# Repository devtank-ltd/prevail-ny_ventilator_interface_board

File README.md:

# prevail-ny_ventilator_interface_board
Interface board for PREVAIL-NY emergency ventilator

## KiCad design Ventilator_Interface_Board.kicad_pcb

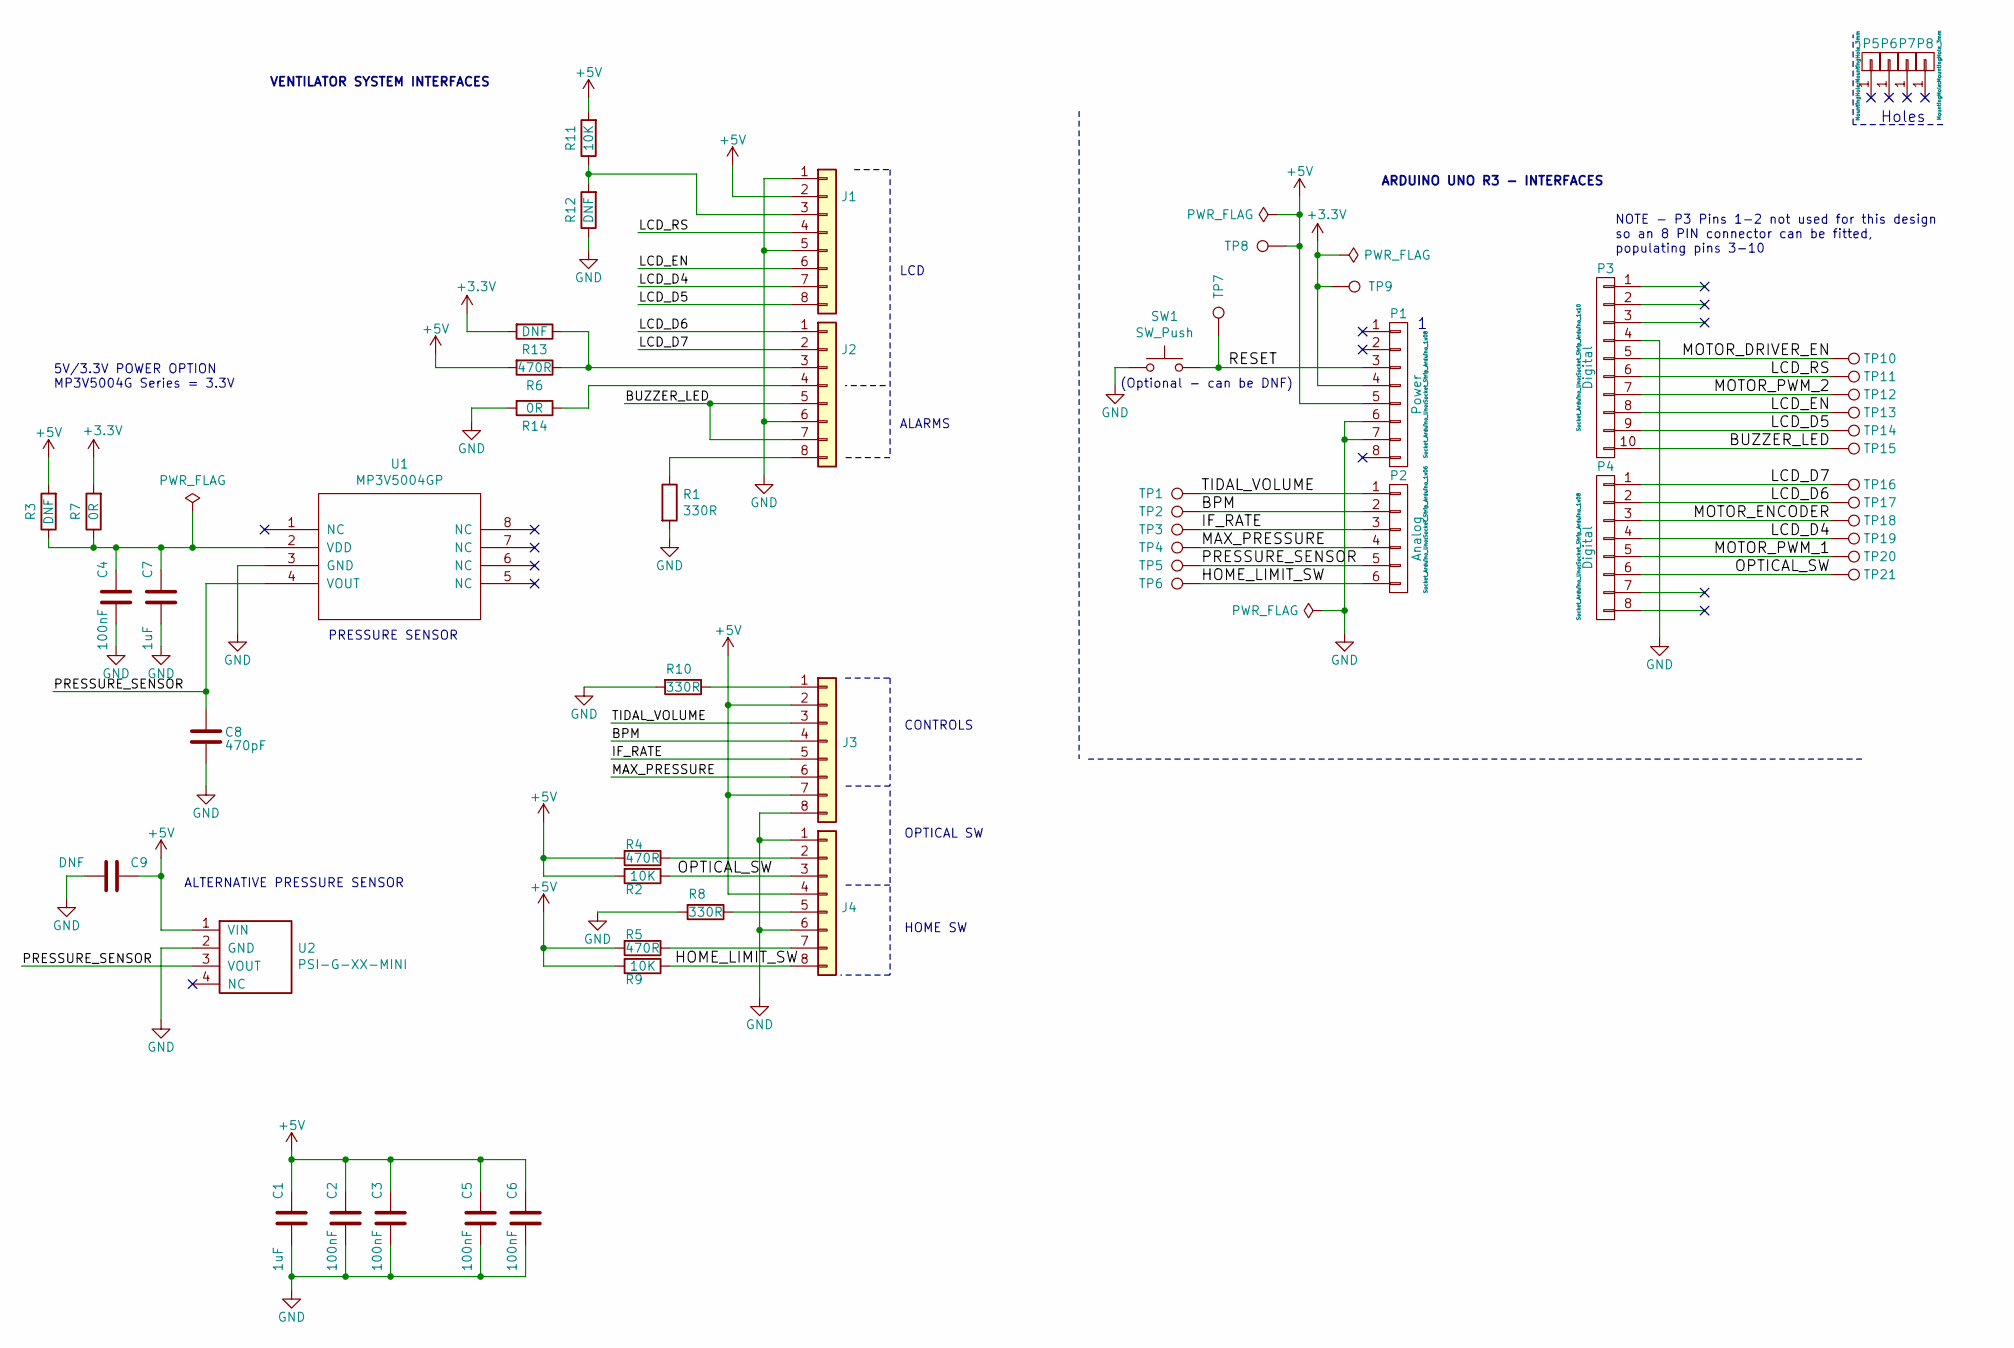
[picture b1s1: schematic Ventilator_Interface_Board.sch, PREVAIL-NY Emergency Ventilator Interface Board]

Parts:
C1, C7: 1uF; C_0603_1608Metric
C2, C3, C4, C5, C6: 100nF; C_0603_1608Metric
C8: 470pF; C_0603_1608Metric
C9: DNF; C_0603_1608Metric
J1, J2, J3, J4: Conn_01x08; PhoenixContact_PTSA_1,5_8-3_5-Z_1x08_P3.50mm_Vertical
P1: Power; Socket_Strip_Arduino_1x08
P2: Analog; Socket_Strip_Arduino_1x06
P3: Digital; Socket_Strip_Arduino_1x10
P4: Digital; Socket_Strip_Arduino_1x08
P5, P6, P7, P8: CONN_01X01; MountingHole_3mm
R1, R8, R10: 330R; R_0603_1608Metric
R2, R9, R11: 10K; R_0603_1608Metric
R3, R12, R13: DNF; R_0603_1608Metric
R4, R5, R6: 470R; R_0603_1608Metric
R7, R14: 0R; R_0603_1608Metric
SW1: SW_Push; SW_SPST_B3U-1000P
TP1, TP2, TP3, TP4, TP5, TP6, TP7, TP8, TP9, TP10, TP11, TP12, TP13, TP14, TP15, TP16, TP17, TP18, TP19, TP20, TP21: TestPoint; TestPoint_THTPad_D1.0mm_Drill0.5mm
U1: MP3V5004GP; SOP_16.8x7.62mm_P2.54mm
U2: PSI-G-XX-MINI; PinHeader_1x04_P2.54mm_Vertical

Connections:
+3V3: P1.4, R7.2, R13.2, TP9.1
+5V: C1.2, C2.2, C3.2, C5.2, C6.2, C9.2, J1.2, J3.2, J3.7, J4.4, P1.5, R2.2, R3.2, R4.2, R5.2, R6.2, R9.2, R11.2, TP8.1, U2.1 (VIN)
/BPM: J3.4, P2.2, TP2.1
/BUZZER_LED: J2.5, J2.7, P3.10, TP15.1
/HOME_LIMIT_SW: J4.8, P2.6, R9.1, TP6.1
/IF_RATE: J3.5, P2.3, TP3.1
/LCD_D4: J1.7, P4.4, TP19.1
/LCD_D5: J1.8, P3.9, TP14.1
/LCD_D6: J2.1, P4.2, TP17.1
/LCD_D7: J2.2, P4.1, TP16.1
/LCD_EN: J1.6, P3.8, TP13.1
/LCD_RS: J1.4, P3.6, TP11.1
/MAX_PRESSURE: J3.6, P2.4, TP4.1
/MOTOR_DRIVER_EN: P3.5, TP10.1
/MOTOR_ENCODER: P4.3, TP18.1
/MOTOR_PWM_1: P4.5, TP20.1
/MOTOR_PWM_2: P3.7, TP12.1
/OPTICAL_SW: J4.3, P4.6, R2.1, TP21.1
/PRESSURE_SENSOR: C8.2, P2.5, TP5.1, U1.4 (VOUT), U2.3 (VOUT)
/RESET: P1.3, SW1.2, TP7.1
/TIDAL_VOLUME: J3.3, P2.1, TP1.1
GND: C1.1, C2.1, C3.1, C4.1, C5.1, C6.1, C7.1, C8.1, C9.1, J1.1, J1.5, J2.6, J3.8, J4.1, J4.6, P1.6, P1.7, P3.4, R1.2, R8.2, R10.2, R12.1, R14.2, SW1.1, U1.3 (GND), U2.2 (GND)
unnamed: C4.2, C7.2, R3.1, R7.1, U1.2 (VDD)
unnamed: J1.3, R11.1, R12.2
unnamed: J2.3, R6.1, R13.1
unnamed: J2.4, R14.1
unnamed: J2.8, R1.1
unnamed: J3.1, R10.1
unnamed: J4.2, R4.1
unnamed: J4.5, R8.1
unnamed: J4.7, R5.1

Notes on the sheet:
Holes
ARDUINO UNO R3 - INTERFACES
VENTILATOR SYSTEM INTERFACES
NOTE - P3 Pins 1-2 not used for this design so an 8 PIN connector can be fitted, populating pins 3-10
5V/3.3V POWER OPTION MP3V5004G Series = 3.3V
LCD
(Optional - can be DNF)
ALARMS
CONTROLS
OPTICAL SW
HOME SW
ALTERNATIVE PRESSURE SENSOR
PRESSURE SENSOR

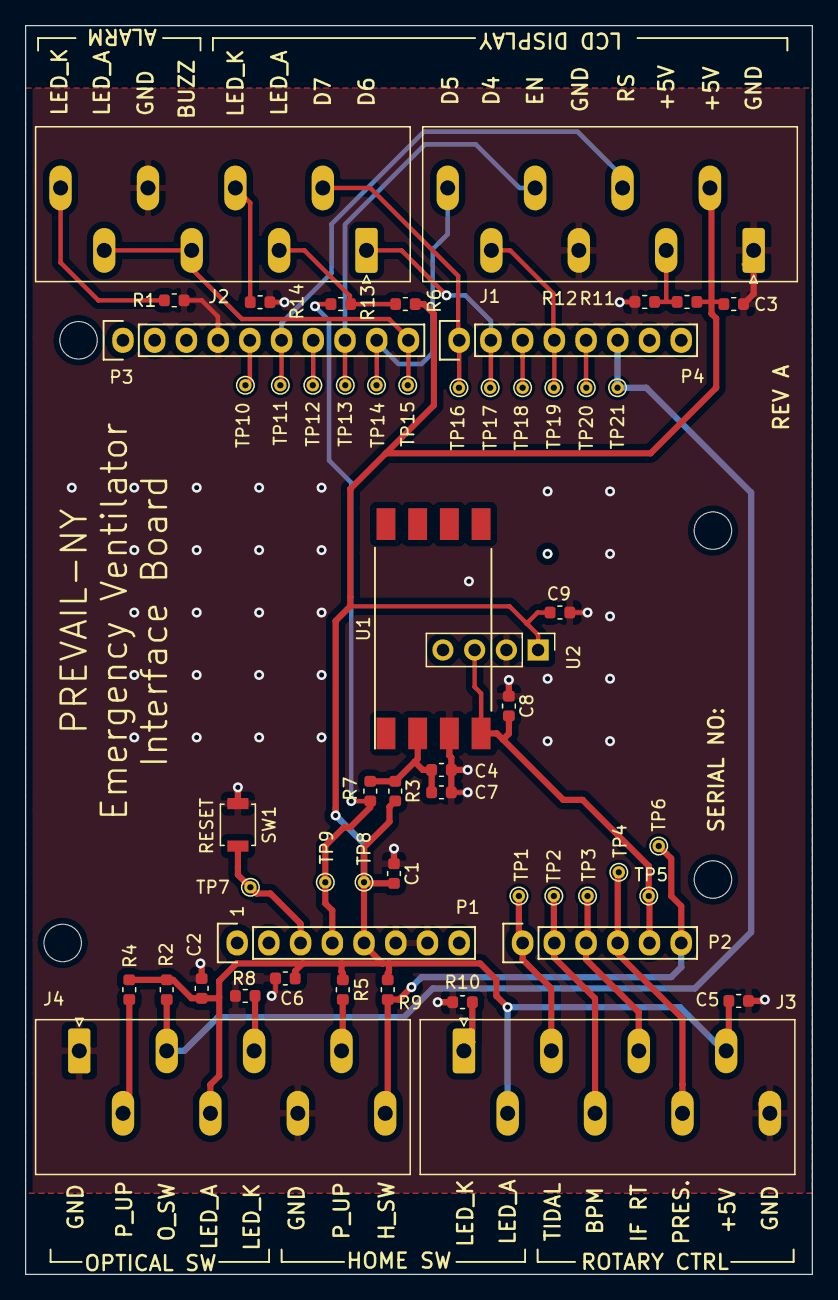
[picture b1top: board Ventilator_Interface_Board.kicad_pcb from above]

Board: 2 copper layers, 63.0 x 100.0 mm, 59 parts (0 on the bottom side), 31 nets.

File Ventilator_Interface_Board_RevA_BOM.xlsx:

Title | PREVAIL-NY Emergency Ventilator Interface Board
Revision | A
Date | 2020-04-17Fri 17 Apr 2020 17:21:26 BST
Generated
Company
Comment 1
Comment 2
Comment 3
Comment 4
Total Parts | 53
Total Unique Parts | 17
Ref | Qty | Value | Footprint | Manufacturer | Manufacturer Part Number | Supplier | Supplier Part number
C2 C3 C4 C5 C6 | 5 | 100nF | Capacitor_SMD:C_0603_1608Metric | Kemet | C0603C104M4RACTU | Digikey | 399-1099-1-ND
C1 C7 | 2 | 1uF | Capacitor_SMD:C_0603_1608Metric | Yageo | CC0603KRX7R7BB105 | Digikey | 311-1446-1-ND
C8 | 1 | 470pF | Capacitor_SMD:C_0603_1608Metric
J1 J2 J3 J4 | 4 | Conn_01x08 | Ventilator:PhoenixContact_PTSA_1 | Phoenix Contact | 1985250 | Digikey | 277-1628-ND
P1 | 1 | Power | Socket_Arduino_Uno:Socket_Strip_Arduino_1x08 | Adafruit Industries | 85 | Digikey | 1528-1074-ND
P2 | 1 | Analog | Socket_Arduino_Uno:Socket_Strip_Arduino_1x06 | Adafruit Industries | 85 | Digikey | 1528-1074-ND | Only one kit required per board
P5 P6 P7 P8 | 4 | CONN_01X01 | Socket_Arduino_Uno:Arduino_1pin
P4 | 1 | Digital | Socket_Arduino_Uno:Socket_Strip_Arduino_1x08 | Adafruit Industries | 85 | Digikey | 1528-1074-ND
P3 | 1 | Digital | Socket_Arduino_Uno:Socket_Strip_Arduino_1x10 | Adafruit Industries | 85 | Digikey | 1528-1074-ND
R5 R4 R6 | 3 | 470R | Resistor_SMD:R_0603_1608Metric | Yageo | RC0603FR-07470RL | Digikey | 311-470HRCT-ND
R8 R10 R1 | 3 | 330R | Resistor_SMD:R_0603_1608Metric | Yageo | RC0603FR-07330RL | Digikey | 311-330HRCT-ND
R2 R9 | 2 | 10K | Resistor_SMD:R_0603_1608Metric | Yageo | RC0603FR-0710KL | Digikey | 311-10.0KHRCT-ND
R3 | 1 | DNF | Resistor_SMD:R_0603_1608Metric
R7 | 1 | 0R | Resistor_SMD:R_0603_1608Metric
SW1 | 1 | SW_Push | Button_Switch_SMD:SW_SPST_B3U-1000P |  | B3U-1000P | Digikey | SW1020CT-ND
TP7 TP1 TP2 TP3 TP4 TP5 TP6 TP8 TP9 TP10 TP11 TP12 TP13 TP14 TP15 TP16 TP17 TP1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 | 21 | TestPoint | TestPoint:TestPoint_THTPad_D1.0mm_Drill0.5mm
U1 | 1 | MP3V5004GP | Ventilator:SOP_16.8x7.62mm_P2.54mm | NXP | MP35004GP | Digikey | MP3V5004GP-ND
Green | Can use equivalent/better
Black | Do not replace/substitute
DNP/DNF | do not populate / do not fit

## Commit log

2020-04-09 added project files
2020-04-17 Rev A - pre-release
2020-04-20 minor changes to make design more flexible
2020-04-21 Rev A released
